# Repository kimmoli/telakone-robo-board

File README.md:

# telakone-robo-board

## Requirements

* Input power supply range 12..50V
* 5V regulator for external stuff (servos, LEDs, ...)
* CPU STM32F407
* RS-485 half-duplex serial interface
* PS2 (playstation) control (SPI)
  * SPI1
    * SPI1_SCK PB3 AF5
    * SPI1_MISO PB4 AF5
    * SPI1_MOSI PB5 AF5
    * SPI_CS_N PA8 OUTPUT
* I2C for external acceleration sensors
  * I2C1
    * I2C1_SCL PB6 AF4
    * I2C1_SDA PB7 AF4
* WS2812B control for LED lights
  * USART2
    * USART2_TX PA2
* USB device interface
  * Virtual serial port
    * OTG_FS_DM PA11 AF10
    * OTG_FS_DP PA12 AF10
	* USB_RENUM PB15 OUTPUT
* Wired UART
  * USART3
    * USART3_TX PD8 AF7
    * USART3_RX PD9 AF7
* RS485 UART
  * USART1
    * USART1_TX PA9 AF7
	* USART1_RX PA10 AF7
	* USART1_TXE PD15 OUTPUT
* Digital outputs
  * 1 enable output for stepper drivers
    * PE14 OUTPUT
  * 6 frequency outputs for stepper drivers
    * TIM4_CH1 PD12 AF2
    * TIM5_CH1 PA0 AF2
    * TIM8_CH1 PC6 AF3
    * TIM9_CH1 PE5 AF3
    * TIM10_CH1 PB8 AF3
    * TIM11_CH1 PB9 AF3
  * 6 direction outputs for stepper drivers
    * PE8 OUTPUT
    * PE9 OUTPUT
    * PE10 OUTPUT
    * PE11 OUTPUT
    * PE12 OUTPUT
    * PE13 OUTPUT
  * 2 servo signal outputs
    * TIM3_CH1 PA6 AF2
    * TIM3_CH2 PA7 AF2
  * 2 high side switch outputs
    * PC0 OUTPUT
    * PC1 OUTPUT
  * 3 debug led outputs
    * PC2 OUTPUT DEBUG (Green)
	* PC3 OUTPUT RUN (Green)
	* PC4 OUTPUT ERROR (Red)
* Digital inputs
  * 16 inputs for limit/zero switches, emergency stop
    * PC8 INPUT
    * PC9 INPUT
    * PC10 INPUT
    * PC11 INPUT
    * PC12 INPUT
    * PC13 INPUT
    * PC14 INPUT
    * PC15 INPUT
    * PD0 INPUT
    * PD1 INPUT
    * PD2 INPUT
    * PD3 INPUT
    * PD4 INPUT
    * PD5 INPUT
    * PD6 INPUT
    * PD7 INPUT

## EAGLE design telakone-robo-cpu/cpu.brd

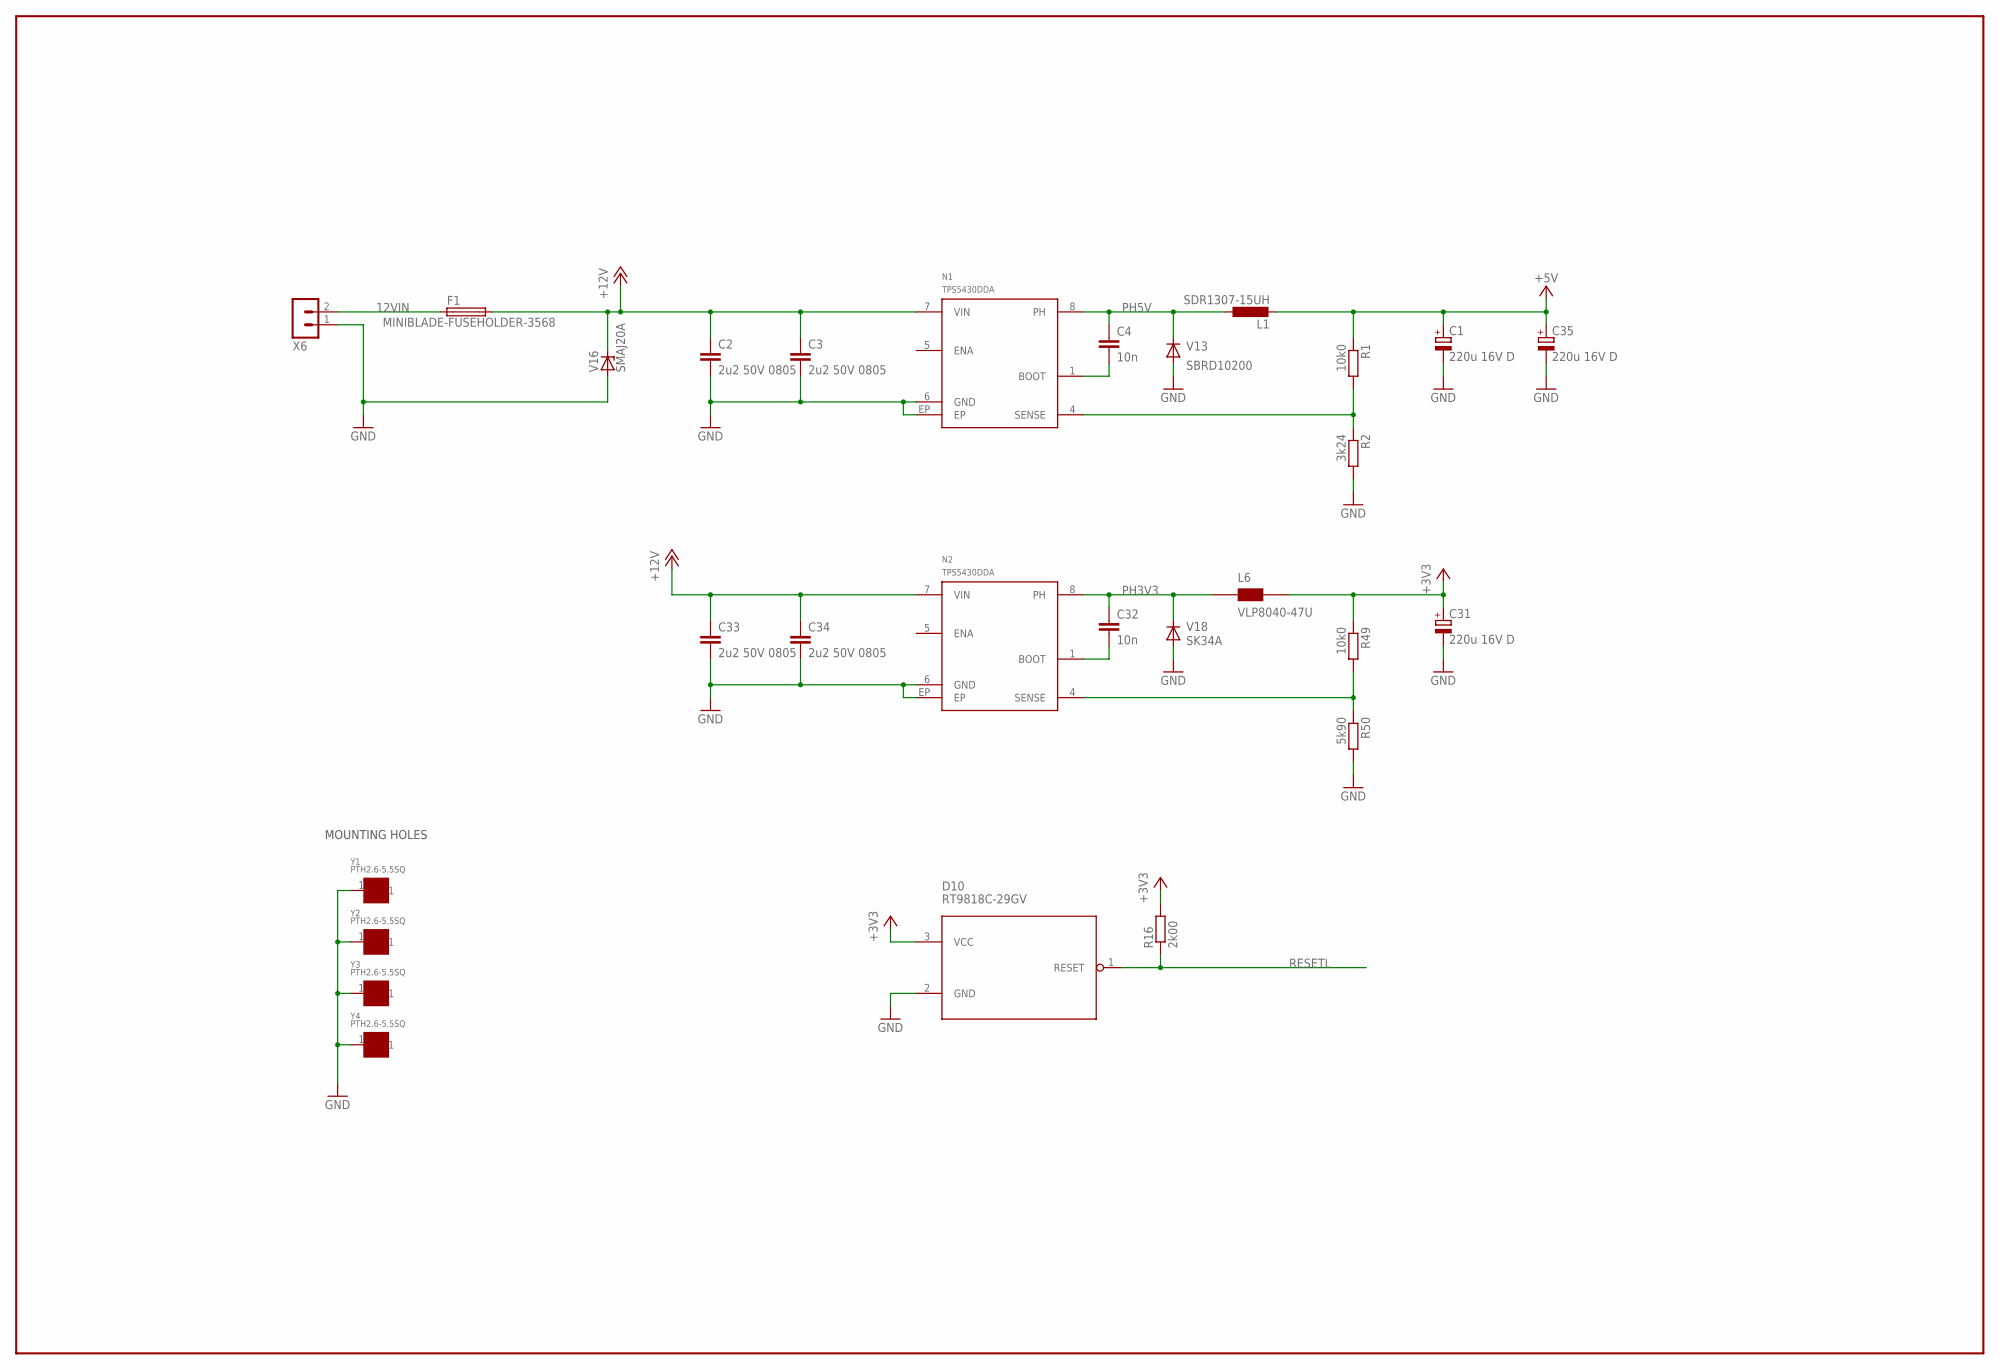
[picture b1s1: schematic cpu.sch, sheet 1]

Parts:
C1, C31, C35: 220u 16V D; CT7343
C2, C3, C33, C34: 2u2 50V 0805; C0805
C4, C32: 10n; C0603
D10: RT9818C-29GV; SOT23
F1: MINIBLADE-FUSEHOLDER-3568; KEYSTONE-3568
L1: SDR1307-15UH; SDR1307
L6: VLP8040-47U; VLP8040
N1, N2: TPS5430DDA; SOIC8-N-EP
R1, R49: 10k0; R0603
R2: 3k24; R0603
R16: 2k00; R0603
R50: 5k90; R0603
V13: SBRD10200; DPACK
V16: SMAJ20A; DO214AC
V18: SK34A; DO214AC
X6: TE_RUUVILIITIN2
Y1, Y2, Y3, Y4: PTH2.6-5.5SQ; PTH-2.6-5.5SQ

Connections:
12VIN: F1.1, F1.4 (1), X6.2
+3V3: C31.+, D10.3 (VCC), L6.2 (B), R16.2, R49.1; also elsewhere on the board
+5V: C1.+, C35.+, L1.2, R1.1; also elsewhere on the board
+12V: C2.1, C3.1, C33.1, C34.1, F1.2, F1.3 (2), N1.7 (VIN), N2.7 (VIN), V16.C; also elsewhere on the board
BOOT3V3: C32.2, N2.1 (BOOT)
BOOT5V: C4.2, N1.1 (BOOT)
GND: C1.-, C2.2, C3.2, C31.-, C33.2, C34.2, C35.-, D10.2 (GND), N1.6 (GND), N1.EP, N2.6 (GND), N2.EP, R2.2, R50.2, V13.1 (A), V13.3 (A), V16.A, V18.A, X6.1, Y1.1, Y2.1, Y3.1, Y4.1; also elsewhere on the board
unnamed: N1.4 (SENSE), R1.2, R2.1
unnamed: N2.4 (SENSE), R49.2, R50.1
PH3V3: C32.1, L6.1 (A), N2.8 (PH), V18.C
PH5V: C4.1, L1.1, N1.8 (PH), V13.2 (C)
RESETL: D10.1 (RESET), R16.1; also elsewhere on the board

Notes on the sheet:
MOUNTING HOLES

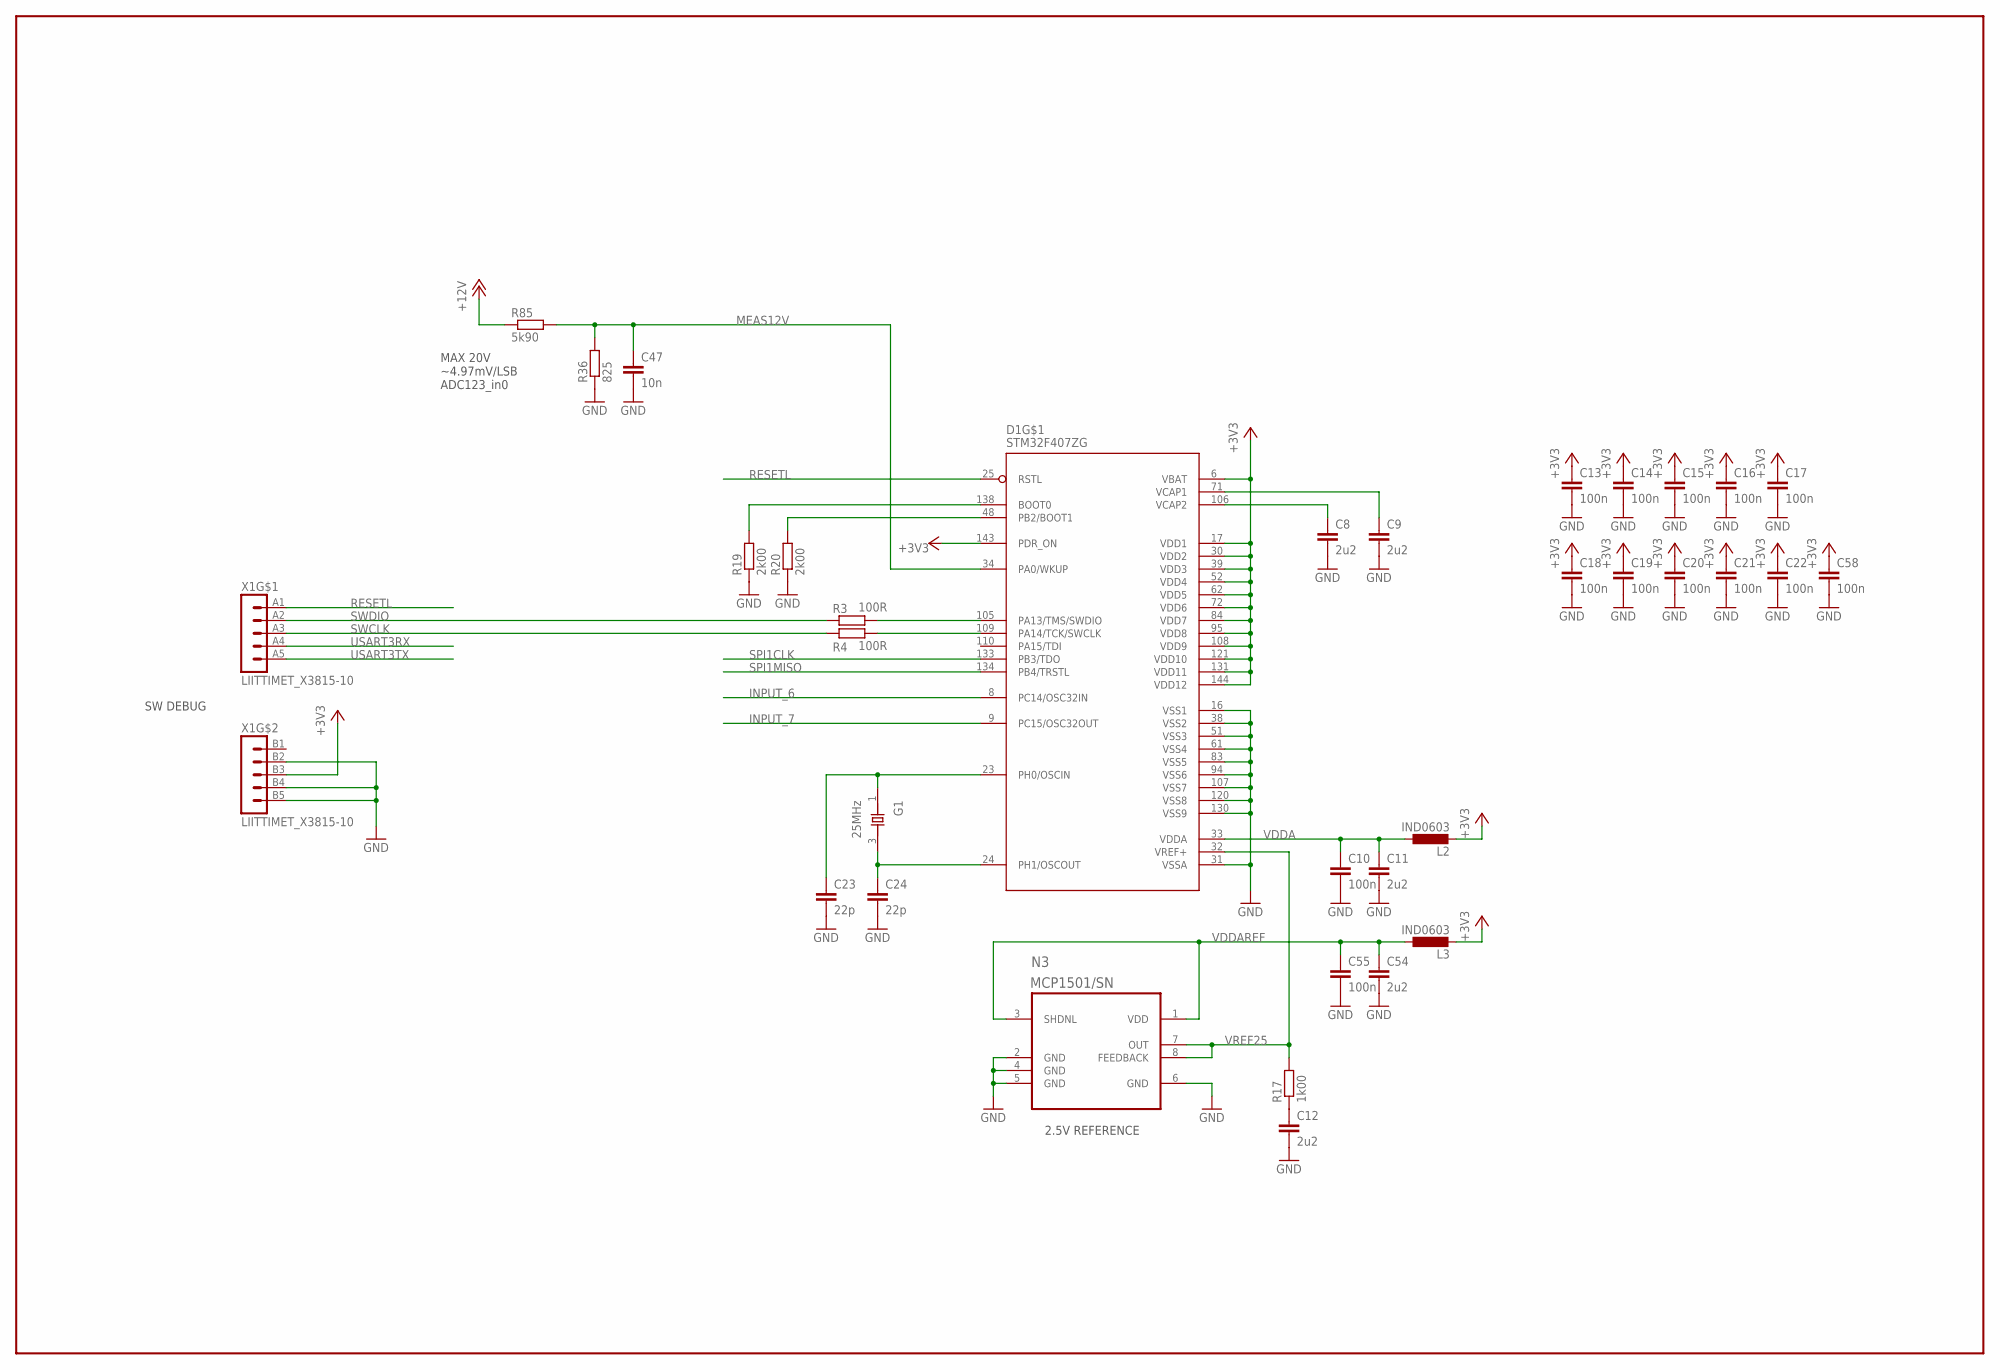
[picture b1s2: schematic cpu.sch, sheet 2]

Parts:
C8, C9, C11, C12, C54: 2u2; C0603
C10, C13, C14, C15, C16, C17, C18, C19, C20, C21, C22, C55, C58: 100n; C0603
C23, C24: 22p; C0603
C47: 10n; C0603
D1: STM32F407ZG; LQFP-144
G1: 25MHz; X_3225
L2, L3: IND0603; R0603
N3: MCP1501/SN; SOIC8-N_MC
R3, R4: 100R; PASSIIVIT_R0603
R17: 1k00; R0603
R19, R20: 2k00; R0603
R36: 825; R0603
R85: 5k90; R0603
X1: LIITTIMET_X3815-10; LIITTIMET_15110102601

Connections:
+3V3: C13.1, C14.1, C15.1, C16.1, C17.1, C18.1, C19.1, C20.1, C21.1, C22.1, C58.1, D1.6 (VBAT), D1.17 (VDD1), D1.30 (VDD2), D1.39 (VDD3), D1.52 (VDD4), D1.62 (VDD5), D1.72 (VDD6), D1.84 (VDD7), D1.95 (VDD8), D1.108 (VDD9), D1.121 (VDD10), D1.131 (VDD11), D1.143 (PDR_ON), D1.144 (VDD12), L2.2, L3.2, X1.B3 (3); also elsewhere on the board
+12V: R85.1; also elsewhere on the board
BOOT0: D1.138 (BOOT0), R19.2
GND: C8.2, C9.2, C10.2, C11.2, C12.2, C13.2, C14.2, C15.2, C16.2, C17.2, C18.2, C19.2, C20.2, C21.2, C22.2, C23.2, C24.2, C47.2, C54.2, C55.2, C58.2, D1.16 (VSS1), D1.31 (VSSA), D1.38 (VSS2), D1.51 (VSS3), D1.61 (VSS4), D1.83 (VSS5), D1.94 (VSS6), D1.107 (VSS7), D1.120 (VSS8), D1.130 (VSS9), N3.2 (GND), N3.4 (GND), N3.5 (GND), N3.6 (GND), R19.1, R20.1, R36.1, X1.B2 (2), X1.B4 (4), X1.B5 (5); also elsewhere on the board
INPUT_6: D1.8 (PC14/OSC32IN); also elsewhere on the board
INPUT_7: D1.9 (PC15/OSC32OUT); also elsewhere on the board
MEAS12V: C47.1, D1.34 (PA0/WKUP), R36.2, R85.2
unnamed: D1.109 (PA14/TCK/SWCLK), R4.2
unnamed: D1.105 (PA13/TMS/SWDIO), R3.2
unnamed: C12.1, R17.1
unnamed: D1.48 (PB2/BOOT1), R20.2
OSCIN: C23.1, D1.23 (PH0/OSCIN), G1.1 (X1)
OSCOUT: C24.1, D1.24 (PH1/OSCOUT), G1.3 (X2)
RESETL: D1.25 (RSTL), X1.A1 (1); also elsewhere on the board
SPI1CLK: D1.133 (PB3/TDO); also elsewhere on the board
SPI1MISO: D1.134 (PB4/TRSTL); also elsewhere on the board
SWCLK: R4.1, X1.A3 (3)
SWDIO: R3.1, X1.A2 (2)
USART3RX: X1.A4 (4); also elsewhere on the board
USART3TX: X1.A5 (5); also elsewhere on the board
VCAP1: C9.1, D1.71 (VCAP1)
VCAP2: C8.1, D1.106 (VCAP2)
VDDA: C10.1, C11.1, D1.33 (VDDA), L2.1
VDDAREF: C54.1, C55.1, L3.1, N3.1 (VDD), N3.3 (SHDNL)
VREF25: D1.32 (VREF+), N3.7 (OUT), N3.8 (FEEDBACK), R17.2

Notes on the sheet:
2.5V REFERENCE
SW DEBUG
MAX 20V ~4.97mV/LSB ADC123_in0

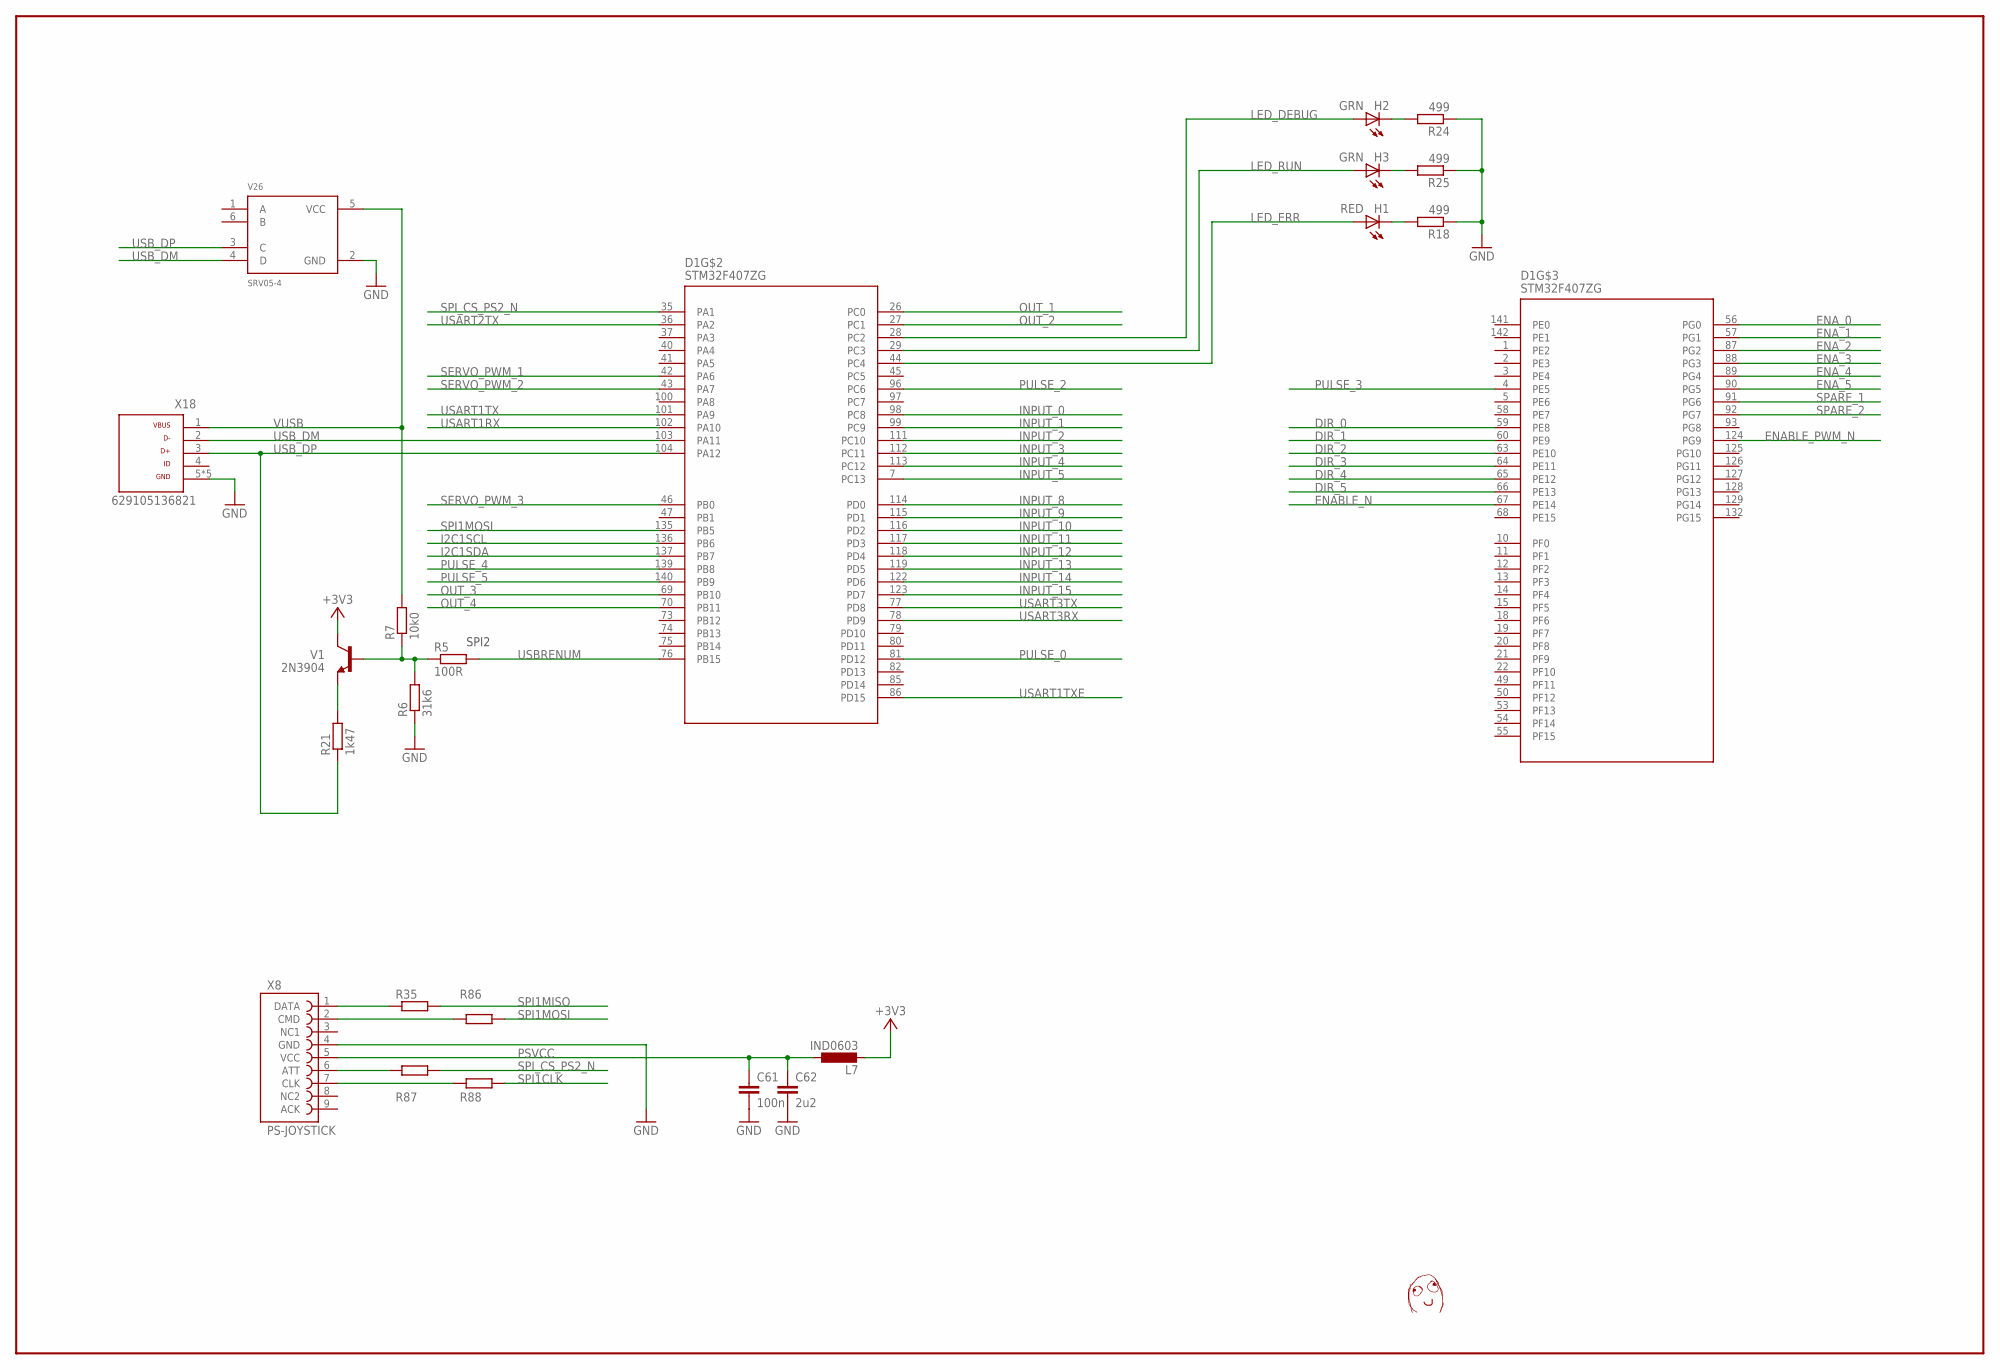
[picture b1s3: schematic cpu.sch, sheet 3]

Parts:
C61: 100n; C0603
C62: 2u2; C0603
D1: STM32F407ZG; LQFP-144
H1: RED; CHIP-LED0603
H2, H3: GRN; CHIP-LED0603
L7: IND0603; R0603
R5: 100R; PASSIIVIT_R0603
R6: 31k6; PASSIIVIT_R0603
R7: 10k0; PASSIIVIT_R0603
R18, R24, R25: 499; R0603
R21: 1k47; PASSIIVIT_R0603
R35, R86, R87, R88: RES0603; OMAT_IC_2_R0603
U$1: DAFUG
V1: 2N3904; OMAT_IC_2_SOT23
V26: SRV05-4; OMAT_IC_2_SOT23-6
X8: PS-JOYSTICK
X18: 629105136821

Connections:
+3V3: L7.2, V1.3 (C); also elsewhere on the board
DIR_0: D1.59 (PE8); also elsewhere on the board
DIR_1: D1.60 (PE9); also elsewhere on the board
DIR_2: D1.63 (PE10); also elsewhere on the board
DIR_3: D1.64 (PE11); also elsewhere on the board
DIR_4: D1.65 (PE12); also elsewhere on the board
DIR_5: D1.66 (PE13); also elsewhere on the board
ENABLE_N: D1.67 (PE14); also elsewhere on the board
ENABLE_PWM_N: D1.124 (PG9); also elsewhere on the board
ENA_0: D1.56 (PG0); also elsewhere on the board
ENA_1: D1.57 (PG1); also elsewhere on the board
ENA_2: D1.87 (PG2); also elsewhere on the board
ENA_3: D1.88 (PG3); also elsewhere on the board
ENA_4: D1.89 (PG4); also elsewhere on the board
ENA_5: D1.90 (PG5); also elsewhere on the board
GND: C61.2, C62.2, R6.1, R18.1, R24.1, R25.1, V26.2 (GND), X8.4 (GND), X18.5, X18.Z1 (5), X18.Z2 (5), X18.Z3 (5), X18.Z4 (5); also elsewhere on the board
I2C1SCL: D1.136 (PB6); also elsewhere on the board
I2C1SDA: D1.137 (PB7); also elsewhere on the board
INPUT_0: D1.98 (PC8); also elsewhere on the board
INPUT_1: D1.99 (PC9); also elsewhere on the board
INPUT_2: D1.111 (PC10); also elsewhere on the board
INPUT_3: D1.112 (PC11); also elsewhere on the board
INPUT_4: D1.113 (PC12); also elsewhere on the board
INPUT_5: D1.7 (PC13); also elsewhere on the board
INPUT_8: D1.114 (PD0); also elsewhere on the board
INPUT_9: D1.115 (PD1); also elsewhere on the board
INPUT_10: D1.116 (PD2); also elsewhere on the board
INPUT_11: D1.117 (PD3); also elsewhere on the board
INPUT_12: D1.118 (PD4); also elsewhere on the board
INPUT_13: D1.119 (PD5); also elsewhere on the board
INPUT_14: D1.122 (PD6); also elsewhere on the board
INPUT_15: D1.123 (PD7); also elsewhere on the board
LED_DEBUG: D1.28 (PC2), H2.A
LED_ERR: D1.44 (PC4), H1.A
LED_RUN: D1.29 (PC3), H3.A
unnamed: R35.1, X8.1 (DATA)
unnamed: R5.1, R6.2, R7.1, V1.1 (B)
unnamed: R21.2, V1.2 (E)
unnamed: R86.1, X8.2 (CMD)
unnamed: H2.C, R24.2
unnamed: H1.C, R18.2
unnamed: H3.C, R25.2
unnamed: R87.1, X8.6 (ATT)
unnamed: R88.1, X8.7 (CLK)
OUT_1: D1.26 (PC0); also elsewhere on the board
OUT_2: D1.27 (PC1); also elsewhere on the board
OUT_3: D1.69 (PB10); also elsewhere on the board
OUT_4: D1.70 (PB11); also elsewhere on the board
PSVCC: C61.1, C62.1, L7.1, X8.5 (VCC)
PULSE_0: D1.81 (PD12); also elsewhere on the board
PULSE_2: D1.96 (PC6); also elsewhere on the board
PULSE_3: D1.4 (PE5); also elsewhere on the board
PULSE_4: D1.139 (PB8); also elsewhere on the board
PULSE_5: D1.140 (PB9); also elsewhere on the board
SERVO_PWM_1: D1.42 (PA6); also elsewhere on the board
SERVO_PWM_2: D1.43 (PA7); also elsewhere on the board
SERVO_PWM_3: D1.46 (PB0); also elsewhere on the board
SPARE_1: D1.91 (PG6); also elsewhere on the board
SPARE_2: D1.92 (PG7); also elsewhere on the board
SPI1CLK: R88.2; also elsewhere on the board
SPI1MISO: R35.2; also elsewhere on the board
SPI1MOSI: D1.135 (PB5), R86.2
SPI_CS_PS2_N: D1.35 (PA1), R87.2
USART1RX: D1.102 (PA10); also elsewhere on the board
USART1TX: D1.101 (PA9); also elsewhere on the board
USART1TXE: D1.86 (PD15); also elsewhere on the board
USART2TX: D1.36 (PA2); also elsewhere on the board
USART3RX: D1.78 (PD9); also elsewhere on the board
USART3TX: D1.77 (PD8); also elsewhere on the board
USBRENUM: D1.76 (PB15), R5.2
USB_DM: D1.103 (PA11), V26.4 (D), X18.2
USB_DP: D1.104 (PA12), R21.1, V26.3 (C), X18.3
VUSB: R7.2, V26.5 (VCC), X18.1

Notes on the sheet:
SPI2

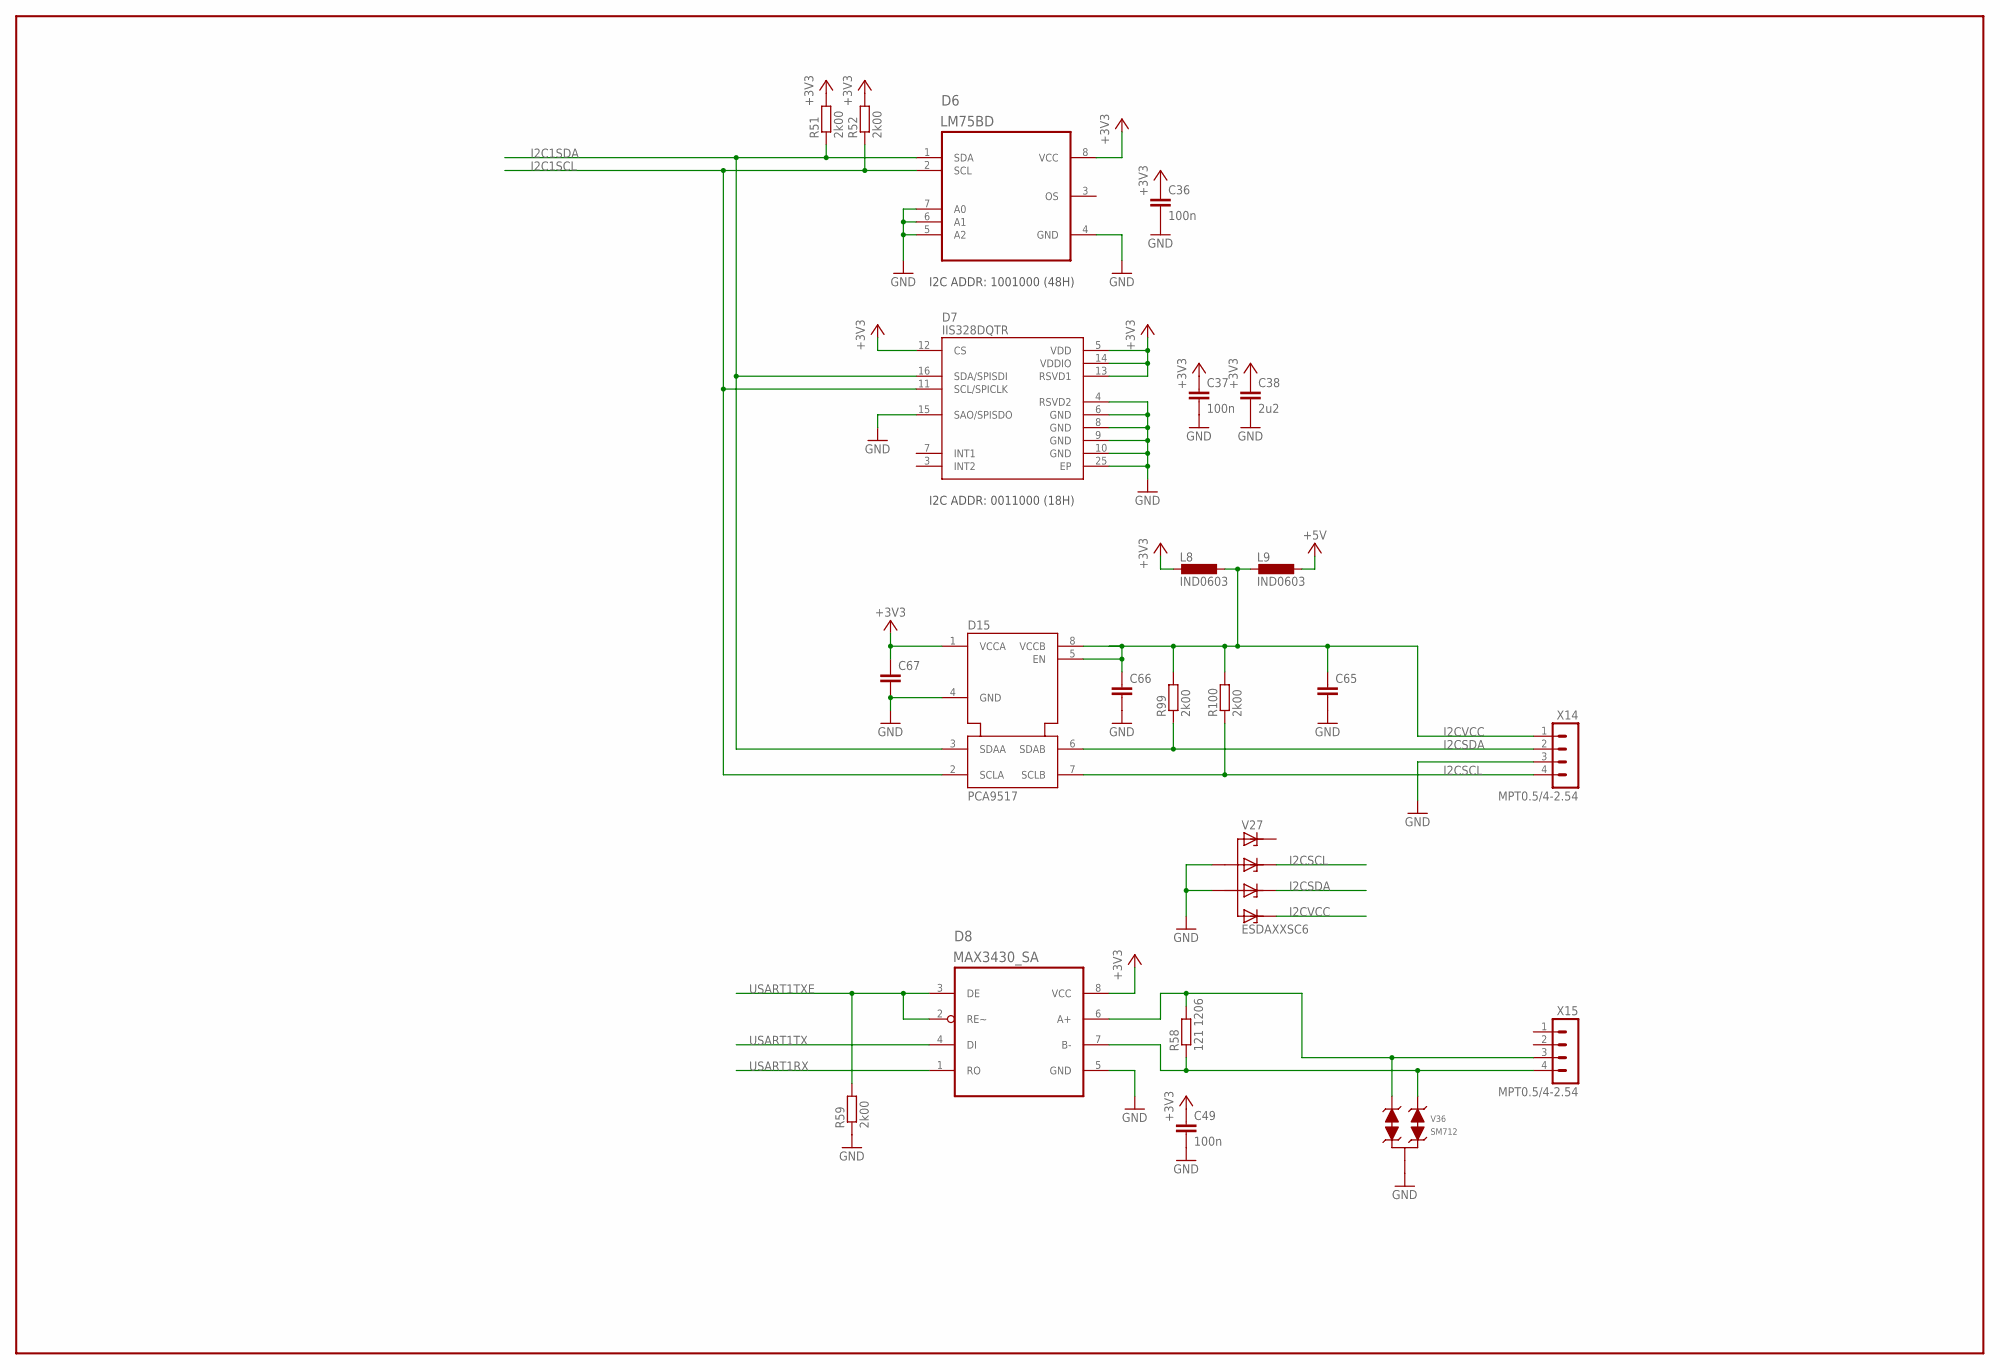
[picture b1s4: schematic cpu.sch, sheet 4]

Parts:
C36, C37, C49: 100n; C0603
C38: 2u2; C0603
C65, C66, C67: CAP0805; OMAT_IC_2_C0805
D6: LM75BD; SOIC8-N_MC
D7: IIS328DQTR; QFN50P400X400X100-25N
D8: MAX3430_SA; SOIC8-N_MC
D15: PCA9517; OMAT_IC_2_SOIC8-N_MC
L8, L9: IND0603; OMAT_IC_2_R0603
R51, R52, R59, R99, R100: 2k00; R0603
R58: 121 1206; R1206
V27: ESDAXXSC6; OMAT_IC_2_SOT23-6
V36: SM712; SOT23
X14, X15: MPT0.5/4-2.54

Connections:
+3V3: C36.1, C37.1, C38.1, C49.1, C67.1, D6.8 (VCC), D7.5 (VDD), D7.12 (CS), D7.13 (RSVD1), D7.14 (VDDIO), D8.8 (VCC), D15.1 (VCCA), L8.2, R51.2, R52.2; also elsewhere on the board
+5V: L9.1; also elsewhere on the board
ACCRTXHI: D8.6 (A+), R58.2, V36.2, X15.3
ACCRTXLO: D8.7 (B-), R58.1, V36.1, X15.4
GND: C36.2, C37.2, C38.2, C49.2, C65.2, C66.2, C67.2, D6.4 (GND), D6.5 (A2), D6.6 (A1), D6.7 (A0), D7.4 (RSVD2), D7.6 (GND), D7.8 (GND), D7.9 (GND), D7.10 (GND), D7.15 (SAO/SPISDO), D7.25 (EP), D8.5 (GND), D15.4 (GND), R59.1, V27.2 (A), V27.5 (A1), V36.3, X14.3; also elsewhere on the board
I2C1SCL: D6.2 (SCL), D7.11 (SCL/SPICLK), D15.2 (SCLA), R52.1; also elsewhere on the board
I2C1SDA: D6.1 (SDA), D7.16 (SDA/SPISDI), D15.3 (SDAA), R51.1; also elsewhere on the board
I2CSCL: D15.7 (SCLB), R100.1, V27.3 (C1), X14.4
I2CSDA: D15.6 (SDAB), R99.1, V27.4 (C2), X14.2
I2CVCC: C65.1, C66.1, D15.5 (EN), D15.8 (VCCB), L8.1, L9.2, R99.2, R100.2, V27.6 (C3), X14.1
USART1RX: D8.1 (RO); also elsewhere on the board
USART1TX: D8.4 (DI); also elsewhere on the board
USART1TXE: D8.2 (RE~), D8.3 (DE), R59.2; also elsewhere on the board

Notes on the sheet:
I2C ADDR: 1001000 (48H)
I2C ADDR: 0011000 (18H)

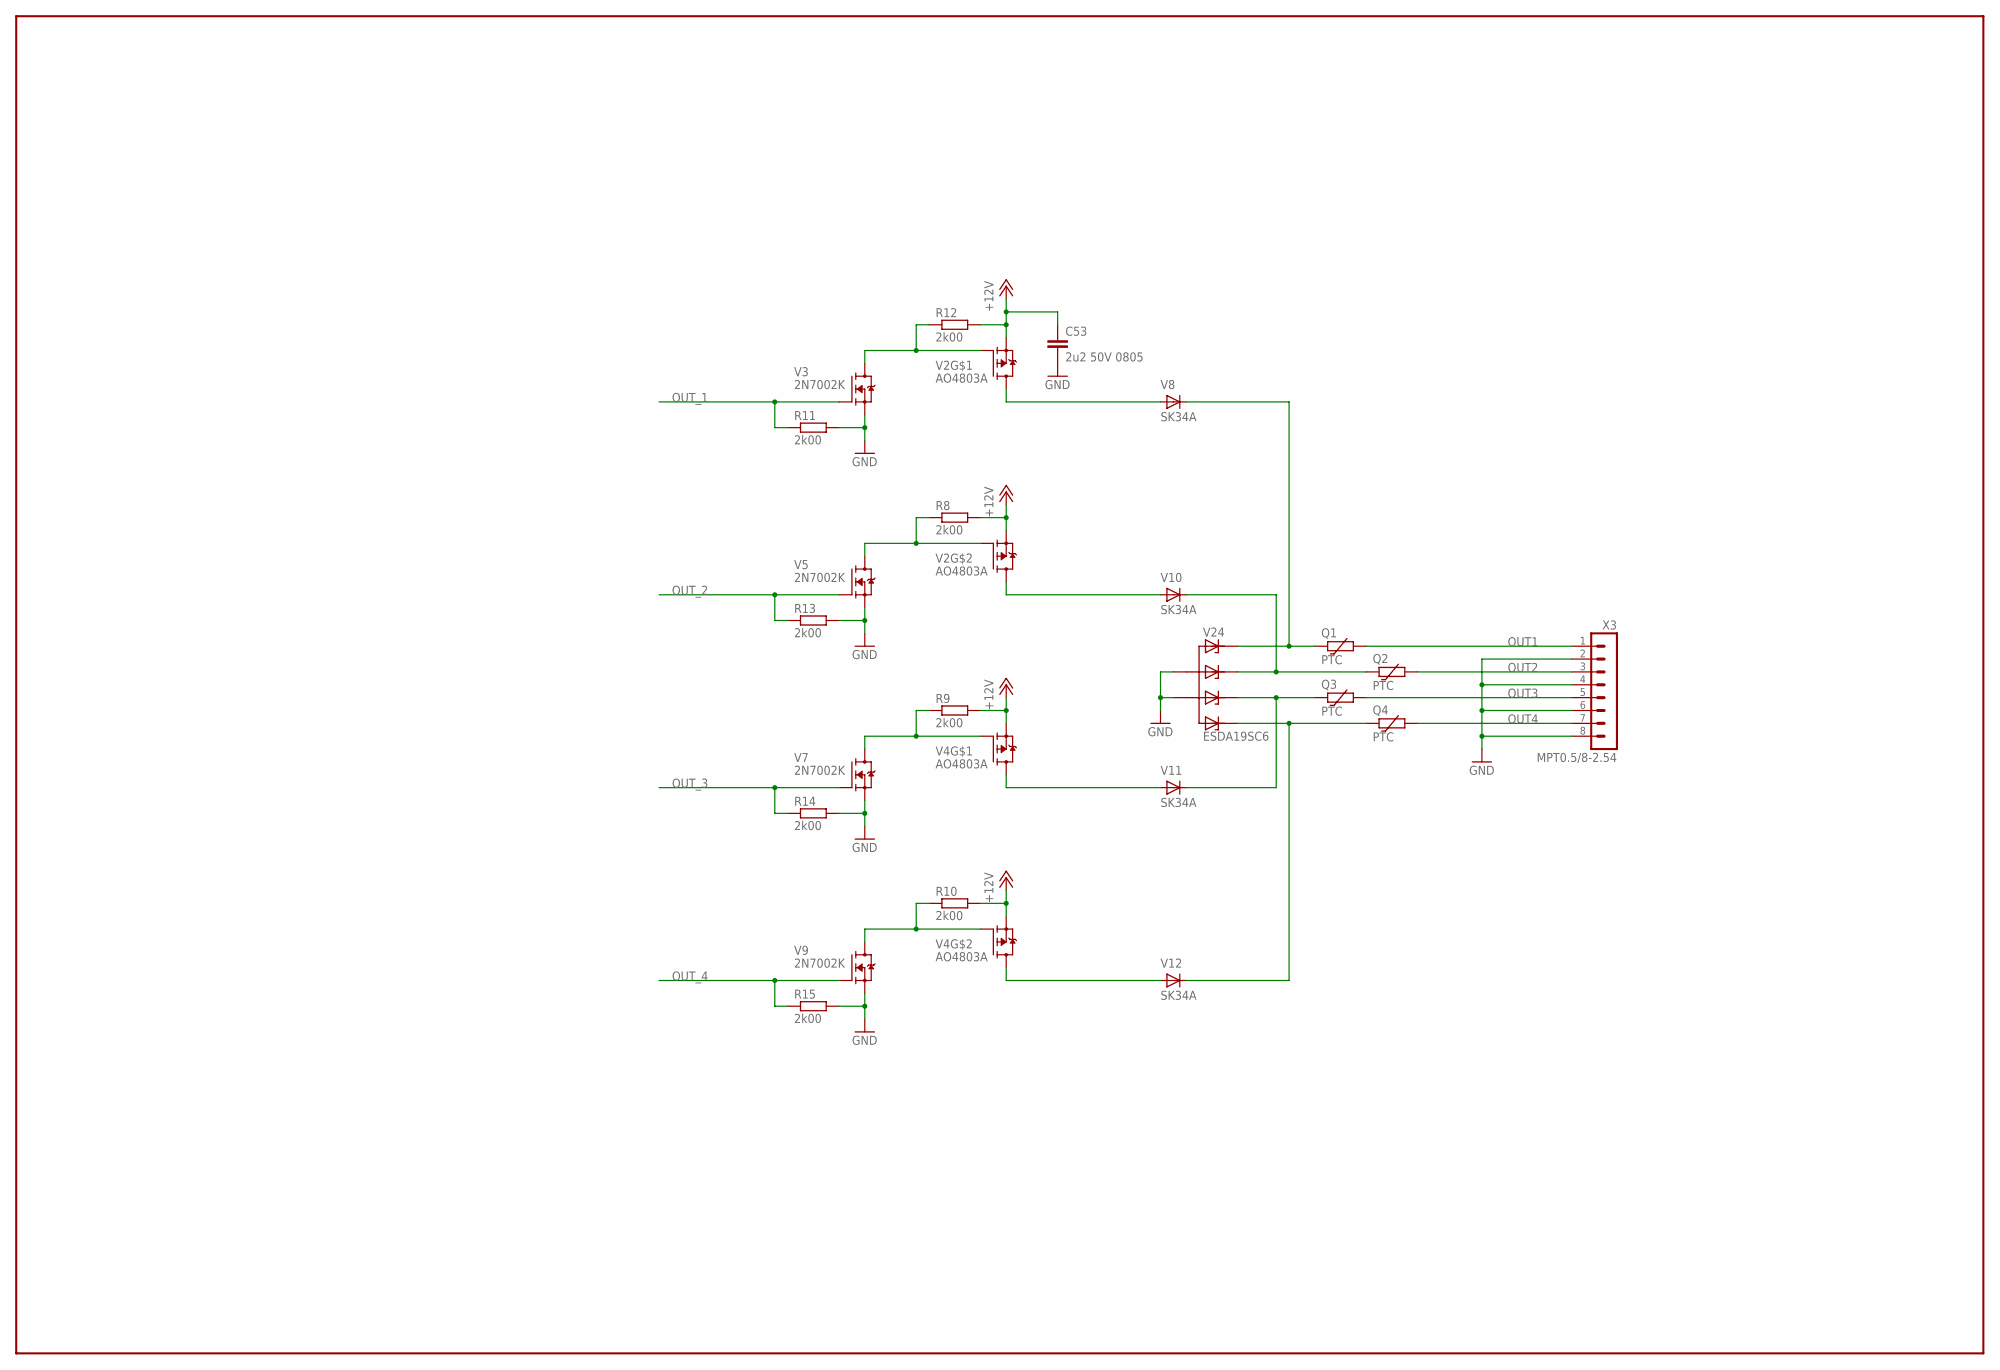
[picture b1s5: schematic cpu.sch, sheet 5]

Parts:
C53: 2u2 50V 0805; C0805
Q1, Q2, Q3, Q4: PTC; OMAT_IC_2_R1812
R8, R9, R10, R11, R12, R13, R14, R15: 2k00; R0603
V2, V4: AO4803A; SOIC8-N_MC
V3, V5, V7, V9: 2N7002K; SOT23
V8, V10, V11, V12: SK34A; DO214AC
V24: ESDA19SC6; SOT23-6
X3: MPT0.5/8-2.54

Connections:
+12V: C53.1, R8.2, R9.2, R10.2, R12.2, V2.1 (S), V2.3 (S), V4.1 (S), V4.3 (S); also elsewhere on the board
GND: C53.2, R11.2, R13.2, R14.2, R15.2, V3.2 (S), V5.2 (S), V7.2 (S), V9.2 (S), V24.2 (A), V24.5 (A1), X3.2, X3.4, X3.6, X3.8; also elsewhere on the board
unnamed: R8.1, V2.2 (G), V5.3 (D)
unnamed: R12.1, V2.4 (G), V3.3 (D)
unnamed: R9.1, V4.4 (G), V7.3 (D)
unnamed: R10.1, V4.2 (G), V9.3 (D)
NERT: V2.5 (D), V2.6 (D), V8.A
NERT1: V2.7 (D), V2.8 (D), V10.A
NERT2: V4.5 (D), V4.6 (D), V11.A
NERT3: V4.7 (D), V4.8 (D), V12.A
OUT1: Q1.2, X3.1
OUT1X: Q1.1, V8.C, V24.1 (C)
OUT2: Q2.2, X3.3
OUT2X: Q2.1, V10.C, V24.3 (C1)
OUT3: Q3.2, X3.5
OUT3X: Q3.1, V11.C, V24.4 (C2)
OUT4: Q4.2, X3.7
OUT4X: Q4.1, V12.C, V24.6 (C3)
OUT_1: R11.1, V3.1 (G); also elsewhere on the board
OUT_2: R13.1, V5.1 (G); also elsewhere on the board
OUT_3: R14.1, V7.1 (G); also elsewhere on the board
OUT_4: R15.1, V9.1 (G); also elsewhere on the board
